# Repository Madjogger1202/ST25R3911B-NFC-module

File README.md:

# ST25R3911B-NFC-module

**NFC-модуль на высокопроизводительном HF-ридере ST25R3911B с управлением от RP2040 и антенной на плате.**

Плата NFC-ридера на чипе **ST25R3911B** (STMicroelectronics) — это заметно более функциональное решение, чем популярные бюджетные модули (PN532, RC522): высокая выходная мощность, поддержка VHBR, автоматическая подстройка антенны и ёмкостный wake-up. Логику и интерфейс берёт на себя **RP2040**, антенна разведена прямо на плате с соблюдением всех рекомендаций ST по согласующим и фильтрующим цепям. После отладки модуль можно смело переиспользовать как ВЧ-фронтенд в составе больших систем.

## Обзор

- **Название проекта:** ST25R3911B-NFC-module
- **Ридер:** STMicroelectronics ST25R3911B — высокопроизводительный HF reader / NFC initiator (13.56 МГц)
- **Микроконтроллер:** Raspberry Pi RP2040
- **Интерфейс ридер ↔ МК:** SPI
- **Антенна:** на плате, с согласующими и фильтрующими цепями по рекомендациям ST
- **Назначение:** отладка ST25R3911B и использование как ВЧ-фронтенда в больших системах

## Ключевые особенности

- **Мультипротокольный HF-ридер** — ISO14443A, ISO14443B (включая высокие битрейты / VHBR), ISO15693, ISO18092 (NFCIP-1, инициатор и активная цель), FeliCa; MIFARE Classic через AFE и framing на стороне МК
- **Высокая выходная мощность** — до 1.4 Вт, два дифференциальных низкоомных (1 Ω) драйвера антенны → большая дальность считывания
- **Автоматическая подстройка антенны (AAT)** — оптимизация под напрямую подключённую антенну
- **Ёмкостный wake-up** — детектирование присутствия карты без включения ВЧ-поля (низкое энергопотребление), плюс детект по амплитуде/фазе
- **Встроенный АЦП** — измерение амплитуды и фазы сигнала на антенне, калибровка
- **Антенна на плате** — разведена с соблюдением рекомендаций ST по фильтрам и согласованию
- **Управление от RP2040** — двухъядерный Cortex-M0+ для логики и обработки

## Что на плате

| Блок | Компонент | Назначение |
|---|---|---|
| NFC-ридер | ST25R3911B | HF reader / NFC initiator, 13.56 МГц |
| Микроконтроллер | RP2040 | Управление, обработка, интерфейс с хостом |
| Антенна | PCB-антенна | Дифференциальная антенна на плате |
| Согласование/фильтры | EMC-фильтр + matching | Цепи по рекомендациям ST (AAT) |
| Интерфейс | USB | Питание и связь с хостом |

## Технические характеристики

| Параметр | Значение |
|---|---|
| Ридер | STMicroelectronics ST25R3911B |
| Рабочая частота | 13.56 МГц |
| Протоколы | ISO14443A/B (+VHBR), ISO15693, ISO18092 (NFCIP-1), FeliCa |
| Выходная мощность | до 1.4 Вт (дифференциальная антенна) |
| Драйверы антенны | 2× дифференциальные, 1 Ω |
| Доп. функции | AAT, ёмкостный wake-up, встроенный АЦП |
| Интерфейс ридера | SPI |
| Микроконтроллер | RP2040, 2× Cortex-M0+ до 133 МГц |
| Питание ридера | 2.4 … 5.5 В |

## Антенна

Антенна выполнена непосредственно на печатной плате. Согласующие и фильтрующие цепи (EMC-фильтр между драйвером и антенной, цепи подстройки) разведены с соблюдением рекомендаций STMicroelectronics, что в связке с автоматической подстройкой антенны (AAT) обеспечивает стабильную работу ВЧ-тракта.

## Применение

- Считыватель карт и меток NFC/RFID (контроль доступа, тикетинг)
- ВЧ-фронтенд для интеграции в большие системы
- Отладка и изучение многопротокольного NFC-ридинга
- Промышленные, медицинские и потребительские NFC-приложения

## Среда разработки

- **Схема и плата:** KiCad
- **Прошивка:** PlatformIO / Arduino / Pico SDK (RP2040), драйвер ST25R3911B (ST RFAL)
- **Документация на компоненты:** datasheet ST25R3911B (ST), RP2040 (Raspberry Pi)

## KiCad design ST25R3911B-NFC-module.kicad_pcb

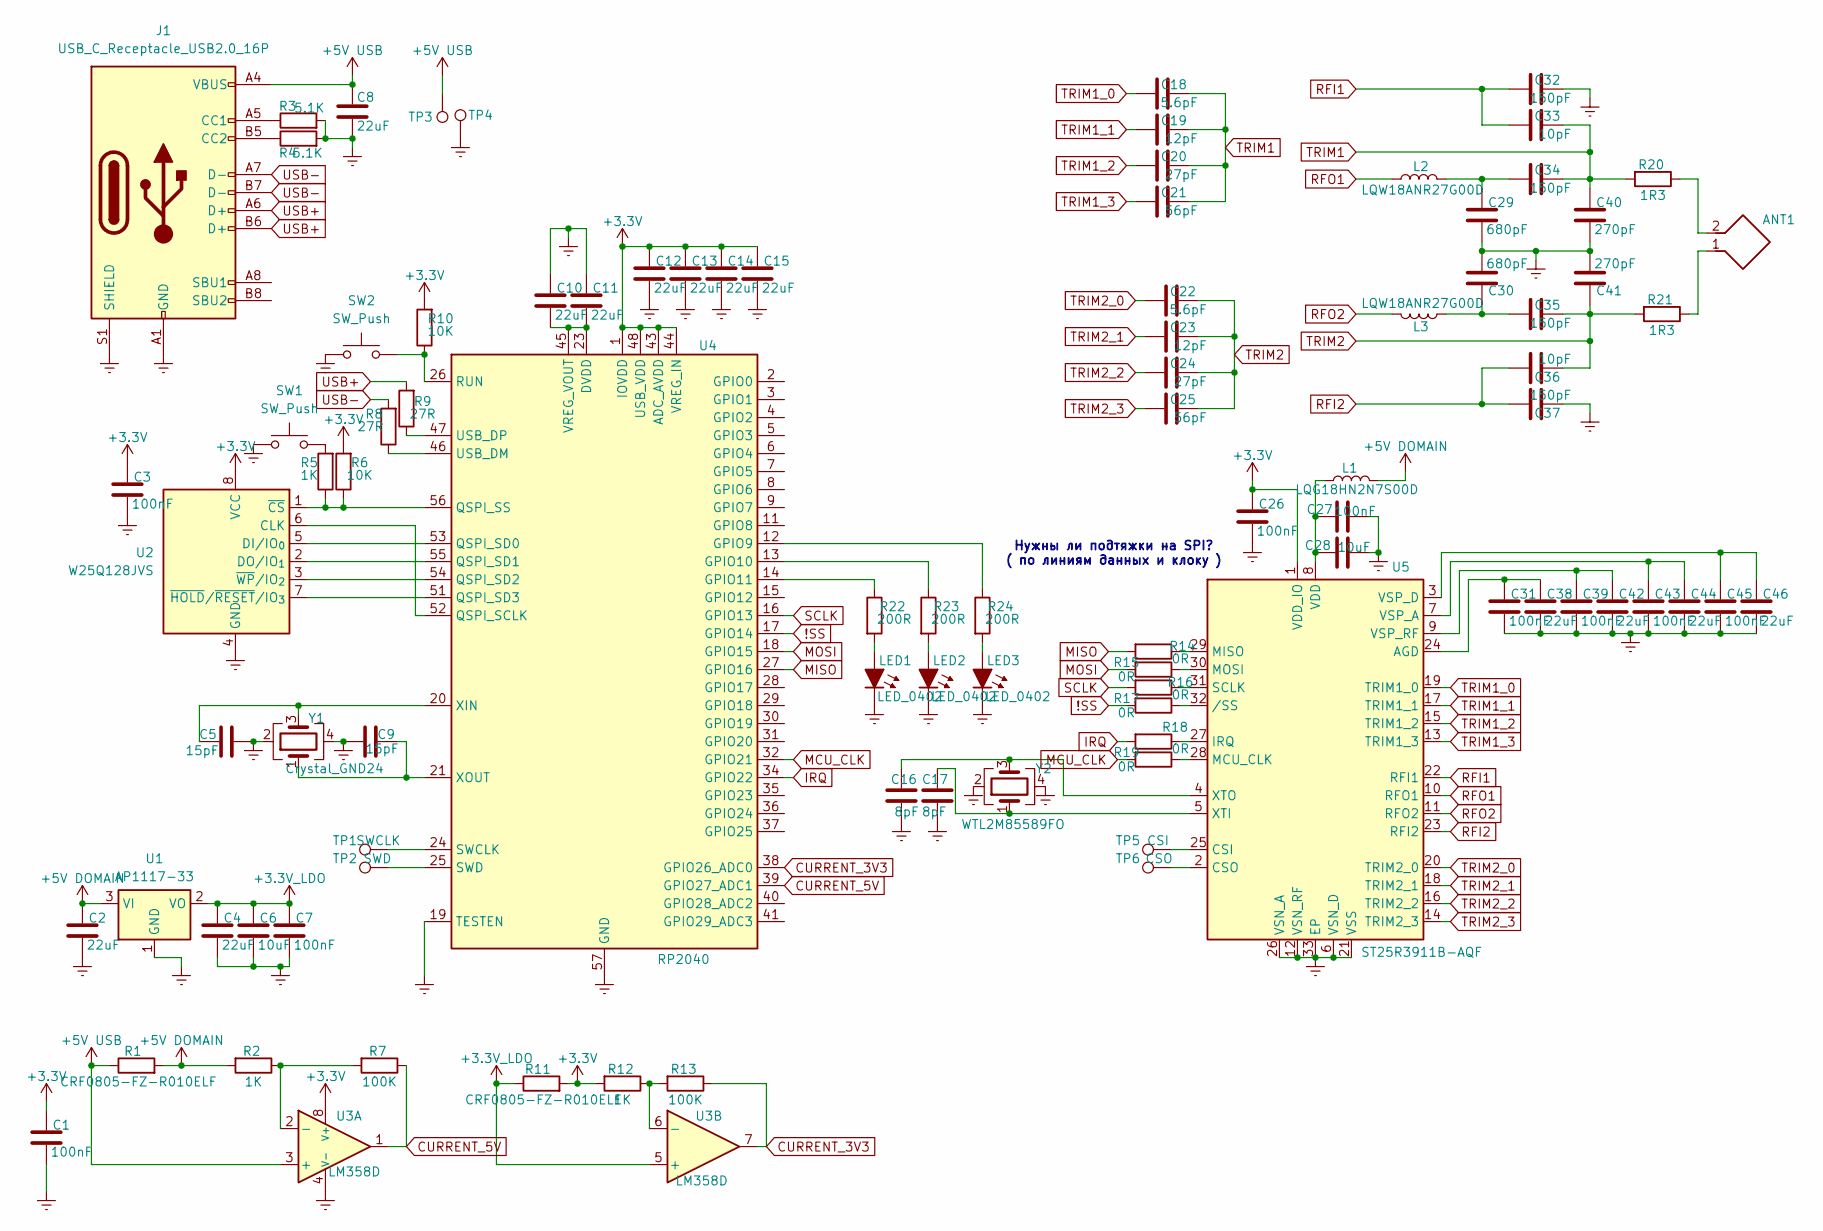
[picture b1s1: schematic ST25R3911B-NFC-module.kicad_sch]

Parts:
ANT1: Без имени
C1, C3, C7, C26, C27, C31, C39, C43, C45: 100nF; C_0402_1005Metric
C2, C4, C8, C10, C11, C12, C13, C14, C15, C38, C42, C44, C46: 22uF; C_0402_1005Metric
C5, C9: 15pF; C_0402_1005Metric
C6, C28: 10uF; C_0402_1005Metric
C16, C17: 8pF; C_0402_1005Metric
C18, C22: 5.6pF; C_0402_1005Metric
C19, C23: 12pF; C_0402_1005Metric
C20, C24: 27pF; C_0402_1005Metric
C21, C25: 56pF; C_0402_1005Metric
C29, C30: 680pF; C_0402_1005Metric
C32, C34, C35, C37: 150pF; C_0402_1005Metric
C33, C36: 10pF; C_0402_1005Metric
C40, C41: 270pF; C_0402_1005Metric
J1: USB_C_Receptacle_USB2.0_16P; USB_C_Receptacle_GCT_USB4105-xx-A_16P_TopMnt_Horizontal
L1: LQG18HN2N7S00D; L_0603_1608Metric
L2, L3: LQW18ANR27G00D; L_0603_1608Metric
LED1, LED2, LED3: LED_0402; LED_0402_1005Metric
R1: CRF0805-FZ-R010ELF; R_0805_2012Metric_Pad1.15x1.40mm
R2, R5, R12: 1K; R_0402_1005Metric
R3, R4: 5.1K; R_0402_1005Metric
R6, R10: 10K; R_0402_1005Metric
R7, R13: 100K; R_0402_1005Metric
R8, R9: 27R; R_0402_1005Metric
R11: CRF0805-FZ-R010ELF; R_0805_2012Metric
R14, R15, R16, R17, R18, R19: 0R; R_0402_1005Metric
R20, R21: 1R3; R_0402_1005Metric
R22, R23, R24: 200R; R_0402_1005Metric
SW1, SW2: SW_Push; SW_SPST_B3U-1000P
TP1: SWCLK; TestPoint_Pad_D1.0mm
TP2: SWD; TestPoint_Pad_D1.0mm
TP3, TP4: TestPoint_Pad_1.5x1.5mm
TP5: CSI; TestPoint_Pad_D1.0mm
TP6: CSO; TestPoint_Pad_D1.0mm
U1: AP1117-33; SOT-223-3_TabPin2
U2: W25Q128JVS; SOIC-8_5.3x5.3mm_P1.27mm
U3: LM358D; SO-8_3.9x4.9mm_P1.27mm
U4: RP2040; QFN-56-1EP_7x7mm_P0.4mm_EP3.2x3.2mm
U5: ST25R3911B-AQF; QFN-32-1EP_5x5mm_P0.5mm_EP3.6x3.6mm_ThermalVias
Y1: Crystal_GND24; Crystal_SMD_Abracon_ABM8G-4Pin_3.2x2.5mm
Y2: WTL2M85589FO; Crystal_SMD_2520-4Pin_2.5x2.0mm

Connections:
!SS: R17.2, U4.17 (GPIO14)
+3.3V: C1.1, C3.1, C12.1, C13.1, C14.1, C15.1, C26.1, R6.2, R10.2, R11.2, R12.2, U2.8 (VCC), U3.8 (V+), U4.1 (IOVDD), U4.10 (IOVDD), U4.22 (IOVDD), U4.33 (IOVDD), U4.42 (IOVDD), U4.43 (ADC_AVDD), U4.44 (VREG_IN), U4.48 (USB_VDD), U4.49 (IOVDD), U5.1 (VDD_IO)
+3.3V_LDO: C4.1, C6.1, C7.1, R11.1, U1.2 (VO), U3.5 (+)
+5V DOMAIN: C2.1, L1.1, R1.2, R2.2, U1.3 (VI)
+5V USB: C8.1, J1.A4 (VBUS), J1.A9 (VBUS), J1.B4 (VBUS), J1.B9 (VBUS), R1.1, TP3.1, U3.3 (+)
CURRENT_3V3: R13.1, U3.7, U4.38 (GPIO26_ADC0)
CURRENT_5V: R7.1, U3.1, U4.39 (GPIO27_ADC1)
Earth: C1.2, C2.2, C3.2, C4.2, C5.2, C6.2, C7.2, C8.2, C9.1, C10.1, C11.1, C12.2, C13.2, C14.2, C15.2, C16.1, C17.2, C26.2, C27.2, C28.2, C29.2, C30.2, C31.2, C32.2, C37.2, C38.2, C39.2, C40.2, C41.2, C42.2, C43.2, C44.2, C45.2, C46.2, J1.A1 (GND), J1.A12 (GND), J1.B1 (GND), J1.B12 (GND), J1.S1 (SHIELD), LED1.1 (K), LED2.1 (K), LED3.1 (K), R3.2, R4.2, SW1.1, SW2.1, TP4.1, U1.1 (GND), U2.4 (GND), U3.4 (V-), U4.19 (TESTEN), U4.57 (GND), U5.6 (VSN_D), U5.12 (VSN_RF), U5.21 (VSS), U5.26 (VSN_A), U5.33 (EP), Y1.2, Y1.4, Y2.2, Y2.4
IRQ: R18.2, U4.34 (GPIO22)
MCU_CLK: R19.2, U4.32 (GPIO21)
MISO: R14.2, U4.27 (GPIO16)
MOSI: R15.2, U4.18 (GPIO15)
unnamed: ANT1.1, R21.1
unnamed: ANT1.2, R20.1
unnamed: C29.1, C34.1, L2.2
unnamed: C30.1, C35.1, L3.2
unnamed: J1.A5 (CC1), R3.1
unnamed: J1.B5 (CC2), R4.1
unnamed: LED1.2 (A), R22.2
unnamed: LED2.2 (A), R23.2
unnamed: LED3.2 (A), R24.2
unnamed: R5.2, SW1.2
unnamed: U2.6 (CLK), U4.52 (QSPI_SCLK)
unnamed: U2.5 (DI/IO_{0}), U4.53 (QSPI_SD0)
unnamed: U2.2 (DO/IO_{1}), U4.55 (QSPI_SD1)
unnamed: R5.1, R6.1, U2.1 (~CS), U4.56 (QSPI_SS)
unnamed: U2.7 (~HOLD/~RESET/IO_{3}), U4.51 (QSPI_SD3)
unnamed: U2.3 (~WP/IO_{2}), U4.54 (QSPI_SD2)
unnamed: R2.1, R7.2, U3.2 (-)
unnamed: R12.1, R13.2, U3.6 (-)
unnamed: R24.1, U4.12 (GPIO9)
unnamed: R23.1, U4.13 (GPIO10)
unnamed: R22.1, U4.14 (GPIO11)
unnamed: R10.1, SW2.2, U4.26 (RUN)
unnamed: TP1.1, U4.24 (SWCLK)
unnamed: TP2.1, U4.25 (SWD)
unnamed: R8.1, U4.46 (USB_DM)
unnamed: R9.1, U4.47 (USB_DP)
unnamed: C10.2, C11.2, U4.23 (DVDD), U4.45 (VREG_VOUT), U4.50 (DVDD)
unnamed: C5.1, U4.20 (XIN), Y1.3
unnamed: C9.2, U4.21 (XOUT), Y1.1
unnamed: C31.1, C38.1, U5.24 (AGD)
unnamed: TP5.1, U5.25 (CSI)
unnamed: TP6.1, U5.2 (CSO)
unnamed: R18.1, U5.27 (IRQ)
unnamed: R19.1, U5.28 (MCU_CLK)
unnamed: R14.1, U5.29 (MISO)
unnamed: R15.1, U5.30 (MOSI)
unnamed: R16.1, U5.31 (SCLK)
unnamed: C27.1, C28.1, L1.2, U5.8 (VDD)
unnamed: C43.1, C44.1, U5.7 (VSP_A)
unnamed: C45.1, C46.1, U5.3 (VSP_D)
unnamed: C39.1, C42.1, U5.9 (VSP_RF)
unnamed: C17.1, U5.5 (XTI), Y2.1
unnamed: C16.2, U5.4 (XTO), Y2.3
unnamed: R17.1, U5.32 (/SS)
RFI1: C32.1, C33.1, U5.22 (RFI1)
RFI2: C36.1, C37.1, U5.23 (RFI2)
RFO1: L2.1, U5.10 (RFO1)
RFO2: L3.1, U5.11 (RFO2)
SCLK: R16.2, U4.16 (GPIO13)
TRIM1: C18.2, C19.2, C20.2, C21.2, C33.2, C34.2, C40.1, R20.2
TRIM1_0: C18.1, U5.19 (TRIM1_0)
TRIM1_1: C19.1, U5.17 (TRIM1_1)
TRIM1_2: C20.1, U5.15 (TRIM1_2)
TRIM1_3: C21.1, U5.13 (TRIM1_3)
TRIM2: C22.2, C23.2, C24.2, C25.2, C35.2, C36.2, C41.1, R21.2
TRIM2_0: C22.1, U5.20 (TRIM2_0)
TRIM2_1: C23.1, U5.18 (TRIM2_1)
TRIM2_2: C24.1, U5.16 (TRIM2_2)
TRIM2_3: C25.1, U5.14 (TRIM2_3)
USB+: J1.A6 (D+), J1.B6 (D+), R9.2
USB-: J1.A7 (D-), J1.B7 (D-), R8.2

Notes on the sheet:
Нужны ли подтяжки на SPI? ( по линиям данных и клоку )

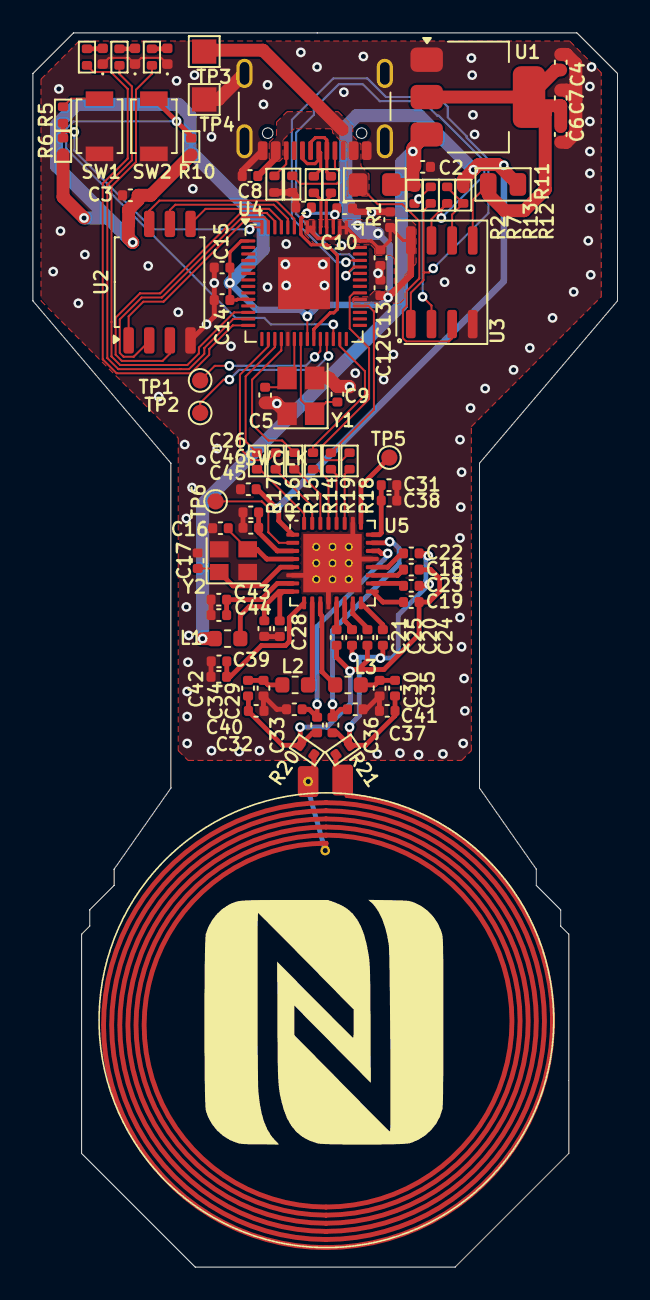
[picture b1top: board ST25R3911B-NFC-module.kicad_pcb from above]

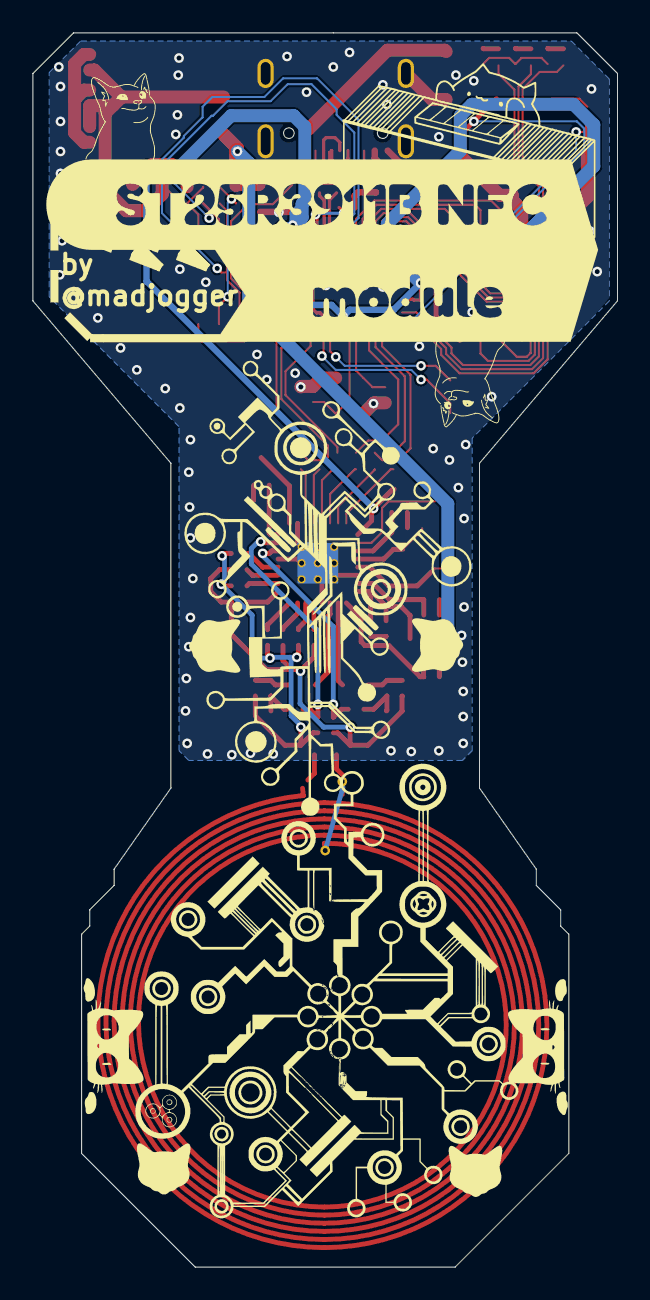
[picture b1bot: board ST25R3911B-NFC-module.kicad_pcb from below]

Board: 2 copper layers, 36.0 x 76.0 mm, 95 parts (2 on the bottom side), 73 nets.

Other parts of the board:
kibuzzard-680CEA90: G***; kibuzzard-680CEA90
kibuzzard-680CEAEF: G***; kibuzzard-680CEAEF

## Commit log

2025-04-23 тык тык
2025-04-24 схему вроде сделал, надо только понять как вообще адекватно, а главное симметрично мне провести к антенне всё что надобно
2025-04-26 rev0 готова
2025-04-27 Добавлено примечание чтобы быстро разобраться если не заработает
2025-04-27 Довёл соединения для АЦП чтения потребления тока для доменов питания
